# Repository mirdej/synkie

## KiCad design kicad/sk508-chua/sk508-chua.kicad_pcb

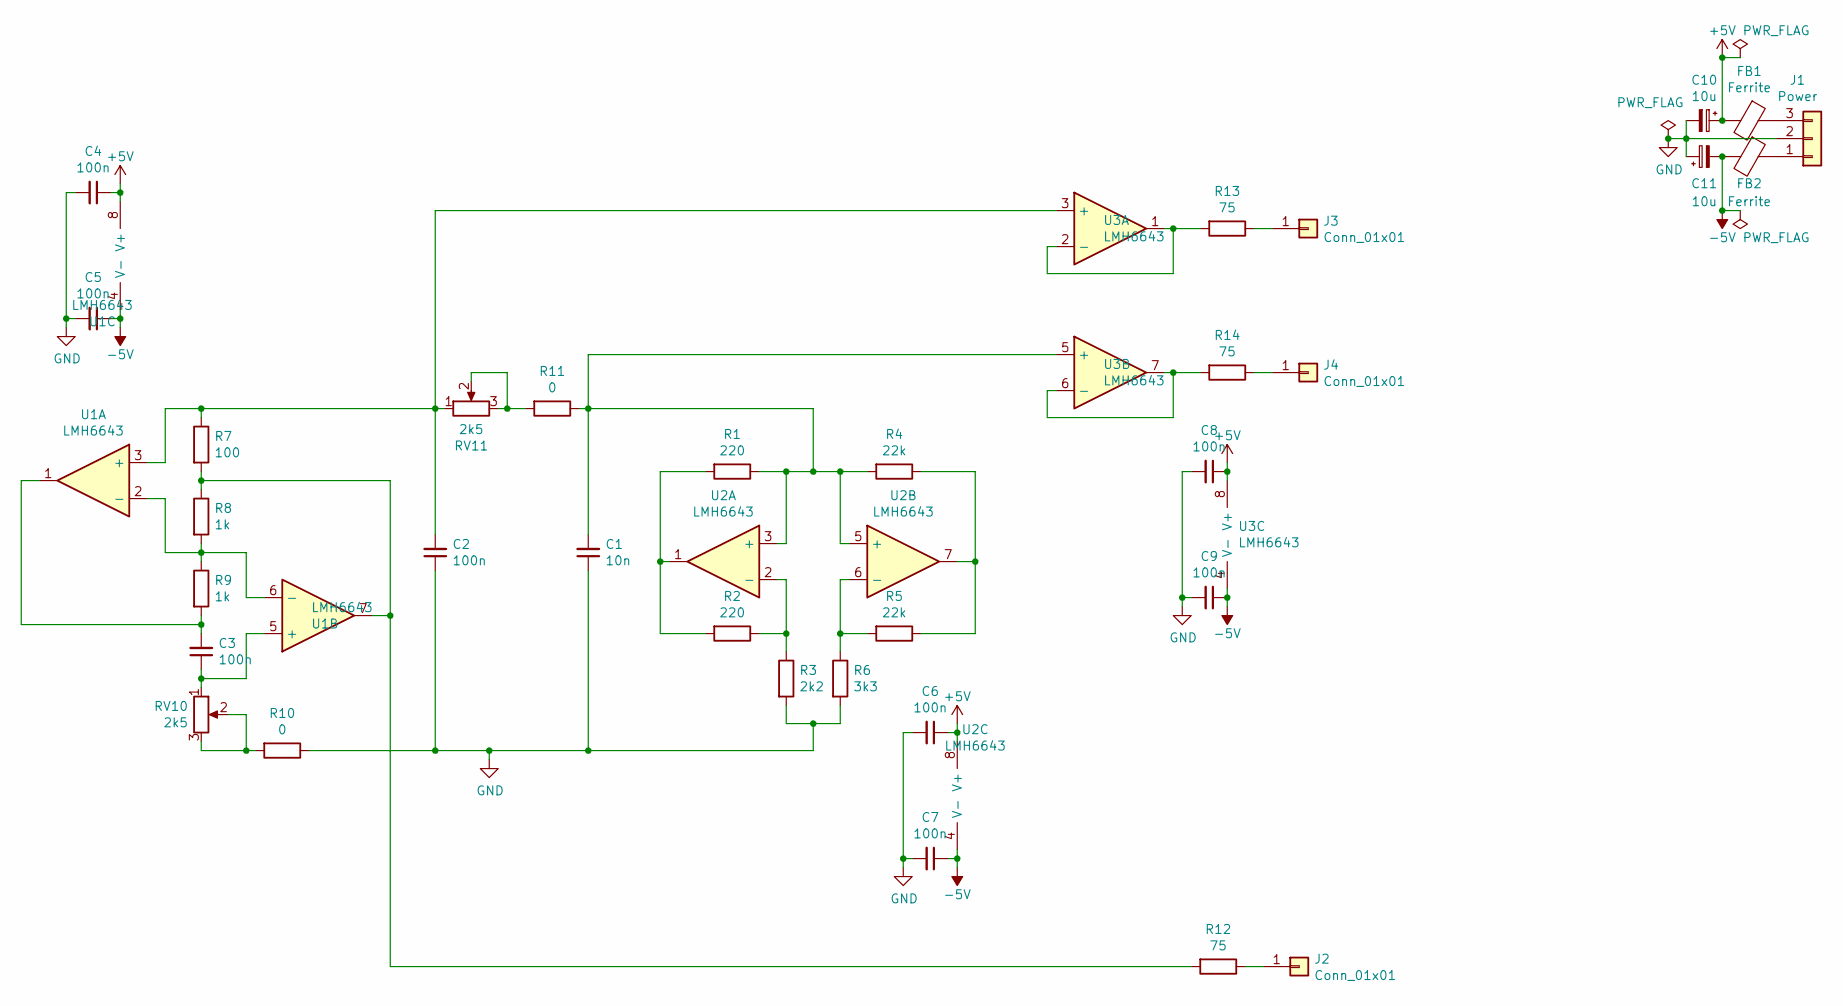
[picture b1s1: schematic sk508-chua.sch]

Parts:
C1: 10n; C_0805_2012Metric_Pad1.15x1.40mm_HandSolder
C2, C3, C4, C5, C6, C7, C8, C9: 100n; C_0603_1608Metric_Pad1.05x0.95mm_HandSolder
C10, C11: 10u; CP_EIA-3528-21_Kemet-B_Pad1.50x2.35mm_HandSolder
FB1, FB2: Ferrite; L_1206_3216Metric_Pad1.42x1.75mm_HandSolder
J1: Power; Molex_KK-254_AE-6410-03A_1x03_P2.54mm_Vertical
J2, J3, J4: Conn_01x01; Solderpad_1mm
R1, R2: 220; R_0805_2012Metric_Pad1.15x1.40mm_HandSolder
R3: 2k2; R_0805_2012Metric_Pad1.15x1.40mm_HandSolder
R4, R5: 22k; R_0805_2012Metric_Pad1.15x1.40mm_HandSolder
R6: 3k3; R_0805_2012Metric_Pad1.15x1.40mm_HandSolder
R7: 100; R_0805_2012Metric_Pad1.15x1.40mm_HandSolder
R8, R9: 1k; R_0805_2012Metric_Pad1.15x1.40mm_HandSolder
R10, R11: 0; R_0805_2012Metric_Pad1.15x1.40mm_HandSolder
R12, R13, R14: 75; R_0805_2012Metric_Pad1.15x1.40mm_HandSolder
RV10, RV11: 2k5; Potentiometer_Alps_RK09L_Single_Horizontal
U1, U2, U3: LMH6643; SOIC-8_3.9x4.9mm_P1.27mm

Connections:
+5V: C4.1, C6.1, C8.1, C10.1, FB1.2, U1.8 (V+), U2.8 (V+), U3.8 (V+)
-5V: C5.1, C7.1, C9.1, C11.2, FB2.2, U1.4 (V-), U2.4 (V-), U3.4 (V-)
GND: C1.1, C2.1, C4.2, C5.2, C6.2, C7.2, C8.2, C9.2, C10.2, C11.1, J1.2, R3.2, R6.2, R10.1
unnamed: C1.2, R1.1, R4.2, R11.1, U2.3 (+), U2.5 (+), U3.5 (+)
unnamed: C2.2, R7.1, RV11.1, U1.3 (+), U3.3 (+)
unnamed: C3.1, RV10.1, U1.5 (+)
unnamed: C3.2, R9.2, U1.1
unnamed: FB1.1, J1.3
unnamed: FB2.1, J1.1
unnamed: J2.1, R12.1
unnamed: J3.1, R13.1
unnamed: J4.1, R14.1
unnamed: R1.2, R2.2, U2.1
unnamed: R2.1, R3.1, U2.2 (-)
unnamed: R4.1, R5.1, U2.7
unnamed: R5.2, R6.1, U2.6 (-)
unnamed: R8.2, R9.1, U1.2 (-), U1.6 (-)
unnamed: R10.2, RV10.2, RV10.3
unnamed: R11.2, RV11.2, RV11.3
unnamed: R7.2, R8.1, R12.2, U1.7
unnamed: R13.2, U3.1, U3.2 (-)
unnamed: R14.2, U3.6 (-), U3.7

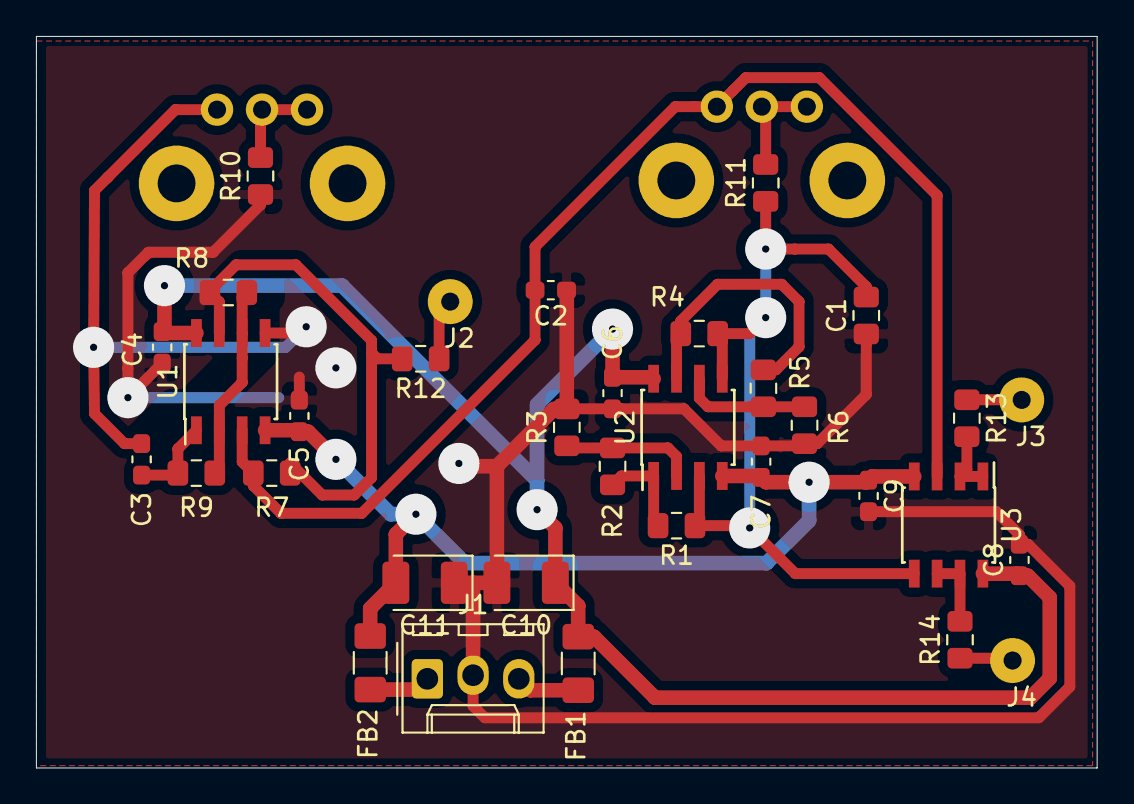
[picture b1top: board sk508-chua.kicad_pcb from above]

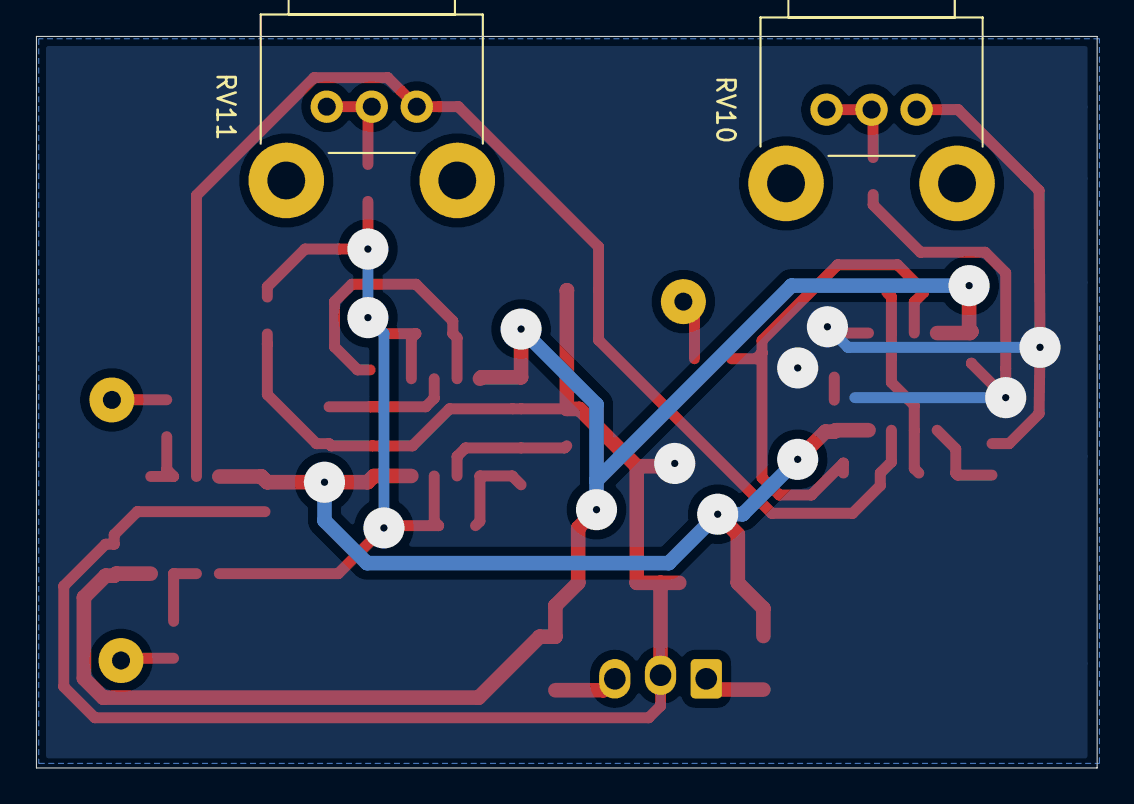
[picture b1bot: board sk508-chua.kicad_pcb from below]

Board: 2 copper layers, 58.9 x 40.6 mm, 36 parts (2 on the bottom side), 22 nets.

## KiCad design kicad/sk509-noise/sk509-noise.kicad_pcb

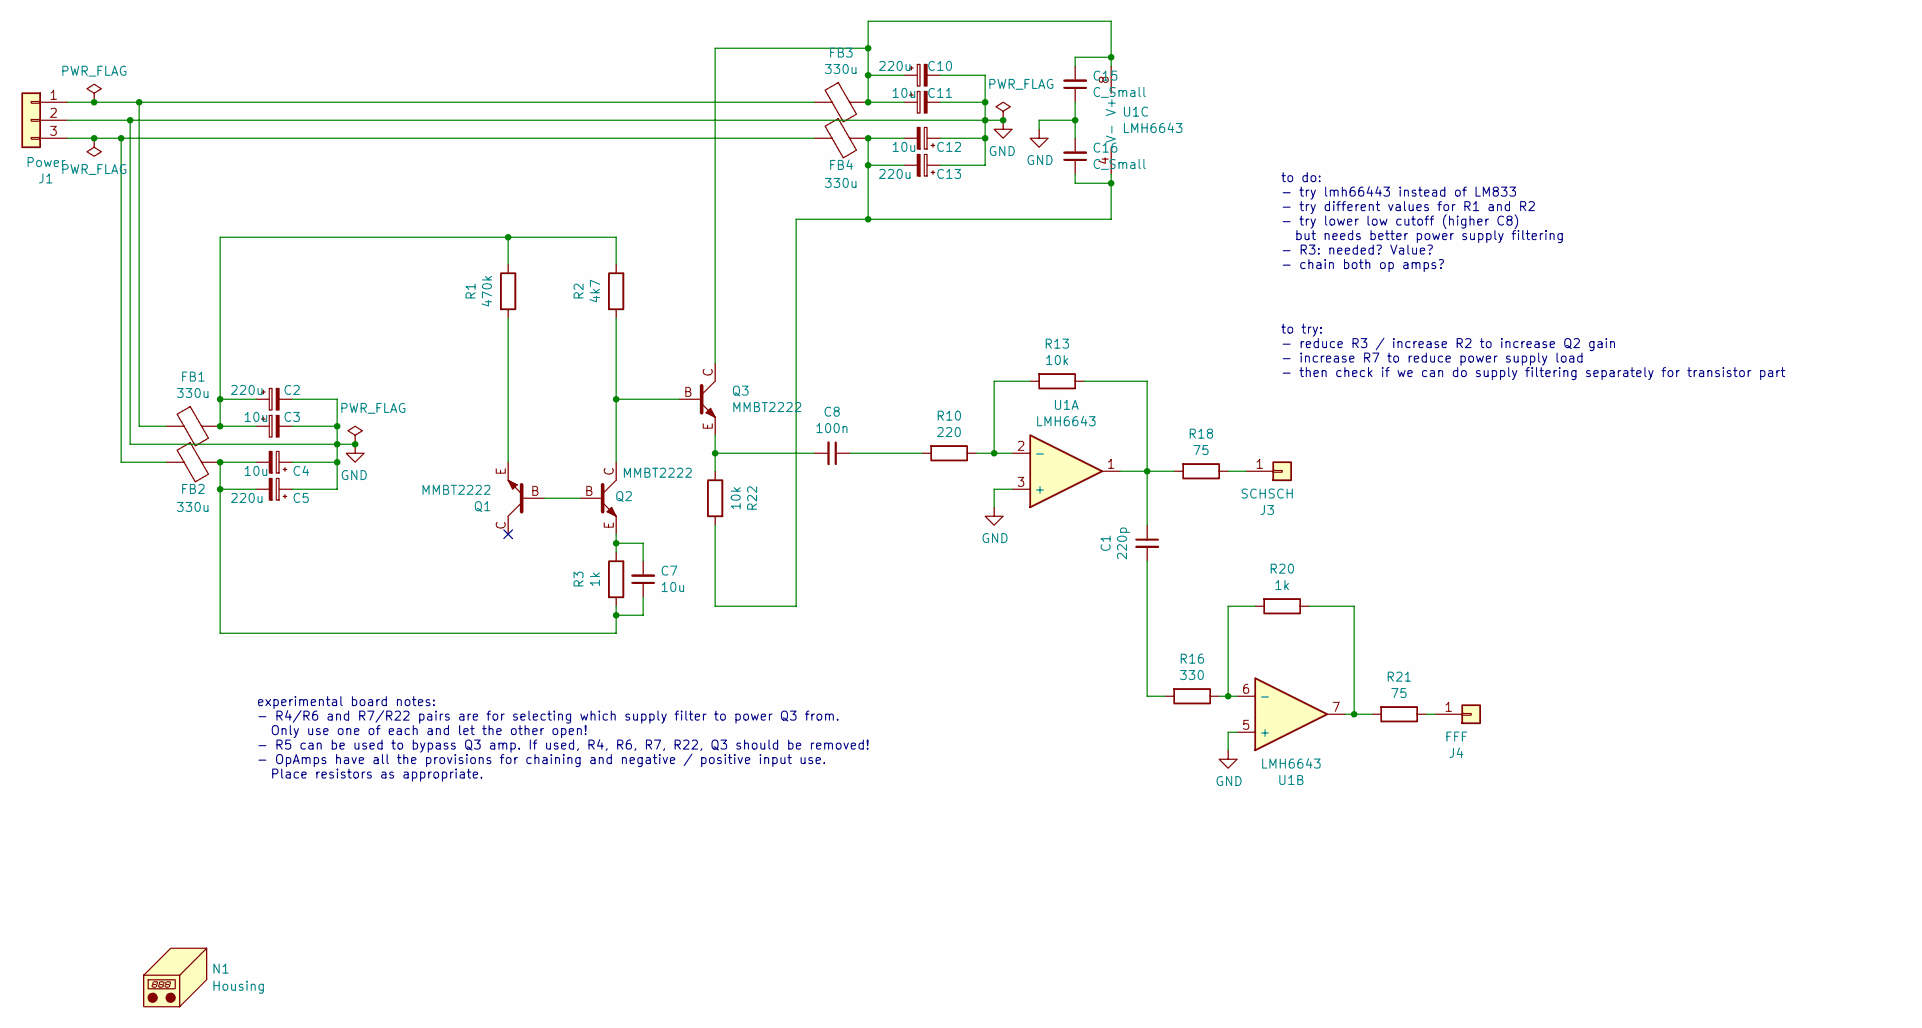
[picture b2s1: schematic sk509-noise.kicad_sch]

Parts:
C1: 220p; C_0805_2012Metric_Pad1.15x1.40mm_HandSolder
C2, C5, C10, C13: 220u; CP_EIA-3528-21_Kemet-B_Pad1.50x2.35mm_HandSolder
C3, C4, C11, C12: 10u; CP_EIA-3528-21_Kemet-B_Pad1.50x2.35mm_HandSolder
C7: 10u; C_0805_2012Metric_Pad1.15x1.40mm_HandSolder
C8: 100n; C_0805_2012Metric_Pad1.15x1.40mm_HandSolder
C15, C16: C_Small; C_0603_1608Metric_Pad1.05x0.95mm_HandSolder
FB1, FB2, FB3, FB4: 330u; L_1206_3216Metric_Pad1.42x1.75mm_HandSolder
J1: Power; Molex_KK-254_AE-6410-03A_1x03_P2.54mm_Vertical_SMD
J3: SCHSCH; Solderpad-SYNKIEPAD-2mm
J4: FFF; Solderpad-SYNKIEPAD-2mm
N1: Housing; Frontplate_20mm
Q1, Q2, Q3: MMBT2222; SOT-23_BEC
R1: 470k; R_0805_2012Metric_Pad1.15x1.40mm_HandSolder
R2: 4k7; R_0805_2012Metric_Pad1.15x1.40mm_HandSolder
R3, R20: 1k; R_0805_2012Metric_Pad1.15x1.40mm_HandSolder
R10: 220; R_0805_2012Metric_Pad1.15x1.40mm_HandSolder
R13, R22: 10k; R_0805_2012Metric_Pad1.15x1.40mm_HandSolder
R16: 330; R_0805_2012Metric_Pad1.15x1.40mm_HandSolder
R18, R21: 75; R_0805_2012Metric_Pad1.15x1.40mm_HandSolder
U1: LMH6643; SOIC-8_3.9x4.9mm_P1.27mm

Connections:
GND: C2.2, C3.2, C4.1, C5.1, C10.2, C11.2, C12.1, C13.1, C15.1, C16.2, J1.2, U1.3 (+), U1.5 (+)
unnamed: C1.1, R13.1, R18.2, U1.1
unnamed: C1.2, R16.2
unnamed: C2.1, C3.1, FB1.2, R1.1, R2.1
unnamed: C4.2, C5.2, C7.1, FB2.2, R3.2
unnamed: C7.2, Q2.E, R3.1
unnamed: C8.1, R10.2
unnamed: C8.2, Q3.E, R22.1
unnamed: FB1.1, FB3.1, J1.1
unnamed: FB2.1, FB4.1, J1.3
unnamed: J3.1, R18.1
unnamed: J4.1, R21.1
unnamed: Q1.B, Q2.B
unnamed: Q1.E, R1.2
unnamed: Q2.C, Q3.B, R2.2
unnamed: R20.1, R21.2, U1.7
unnamed: R10.1, R13.2, U1.2 (-)
unnamed: R16.1, R20.2, U1.6 (-)
unnamed: C10.1, C11.1, C15.2, FB3.2, Q3.C, U1.8 (V+)
unnamed: C12.2, C13.2, C16.1, FB4.2, R22.2, U1.4 (V-)

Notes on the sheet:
to do: - try lmh66443 instead of LM833 - try different values for R1 and R2 - try lower low cutoff (higher C8) but needs better power supply filtering - R3: needed? Value? - chain both op amps?
experimental board notes: - R4/R6 and R7/R22 pairs are for selecting which supply filter to power Q3 from. Only use one of each and let the other open! - R5 can be used to bypass Q3 amp. If used, R4, R6, R7, R22, Q3 should be removed! - OpAmps have all the provisions for chaining and negative / pos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
to try: - reduce R3 / increase R2 to increase Q2 gain - increase R7 to reduce power supply load - then check if we can do supply filtering separately for transistor part

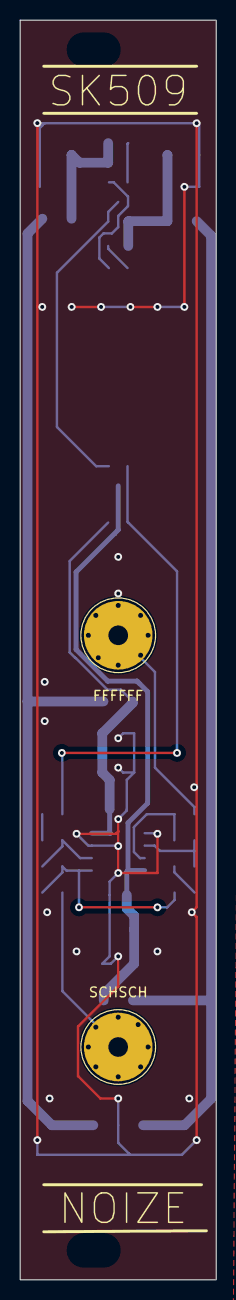
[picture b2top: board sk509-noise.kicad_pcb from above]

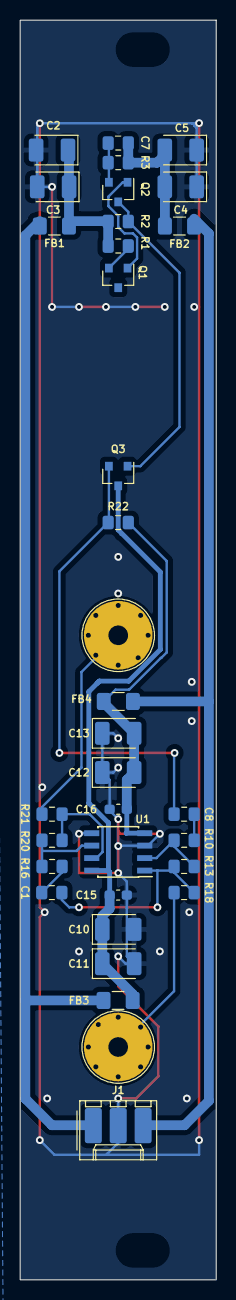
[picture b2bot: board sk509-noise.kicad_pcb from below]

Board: 2 copper layers, 20.0 x 128.5 mm, 35 parts (32 on the bottom side), 20 nets.

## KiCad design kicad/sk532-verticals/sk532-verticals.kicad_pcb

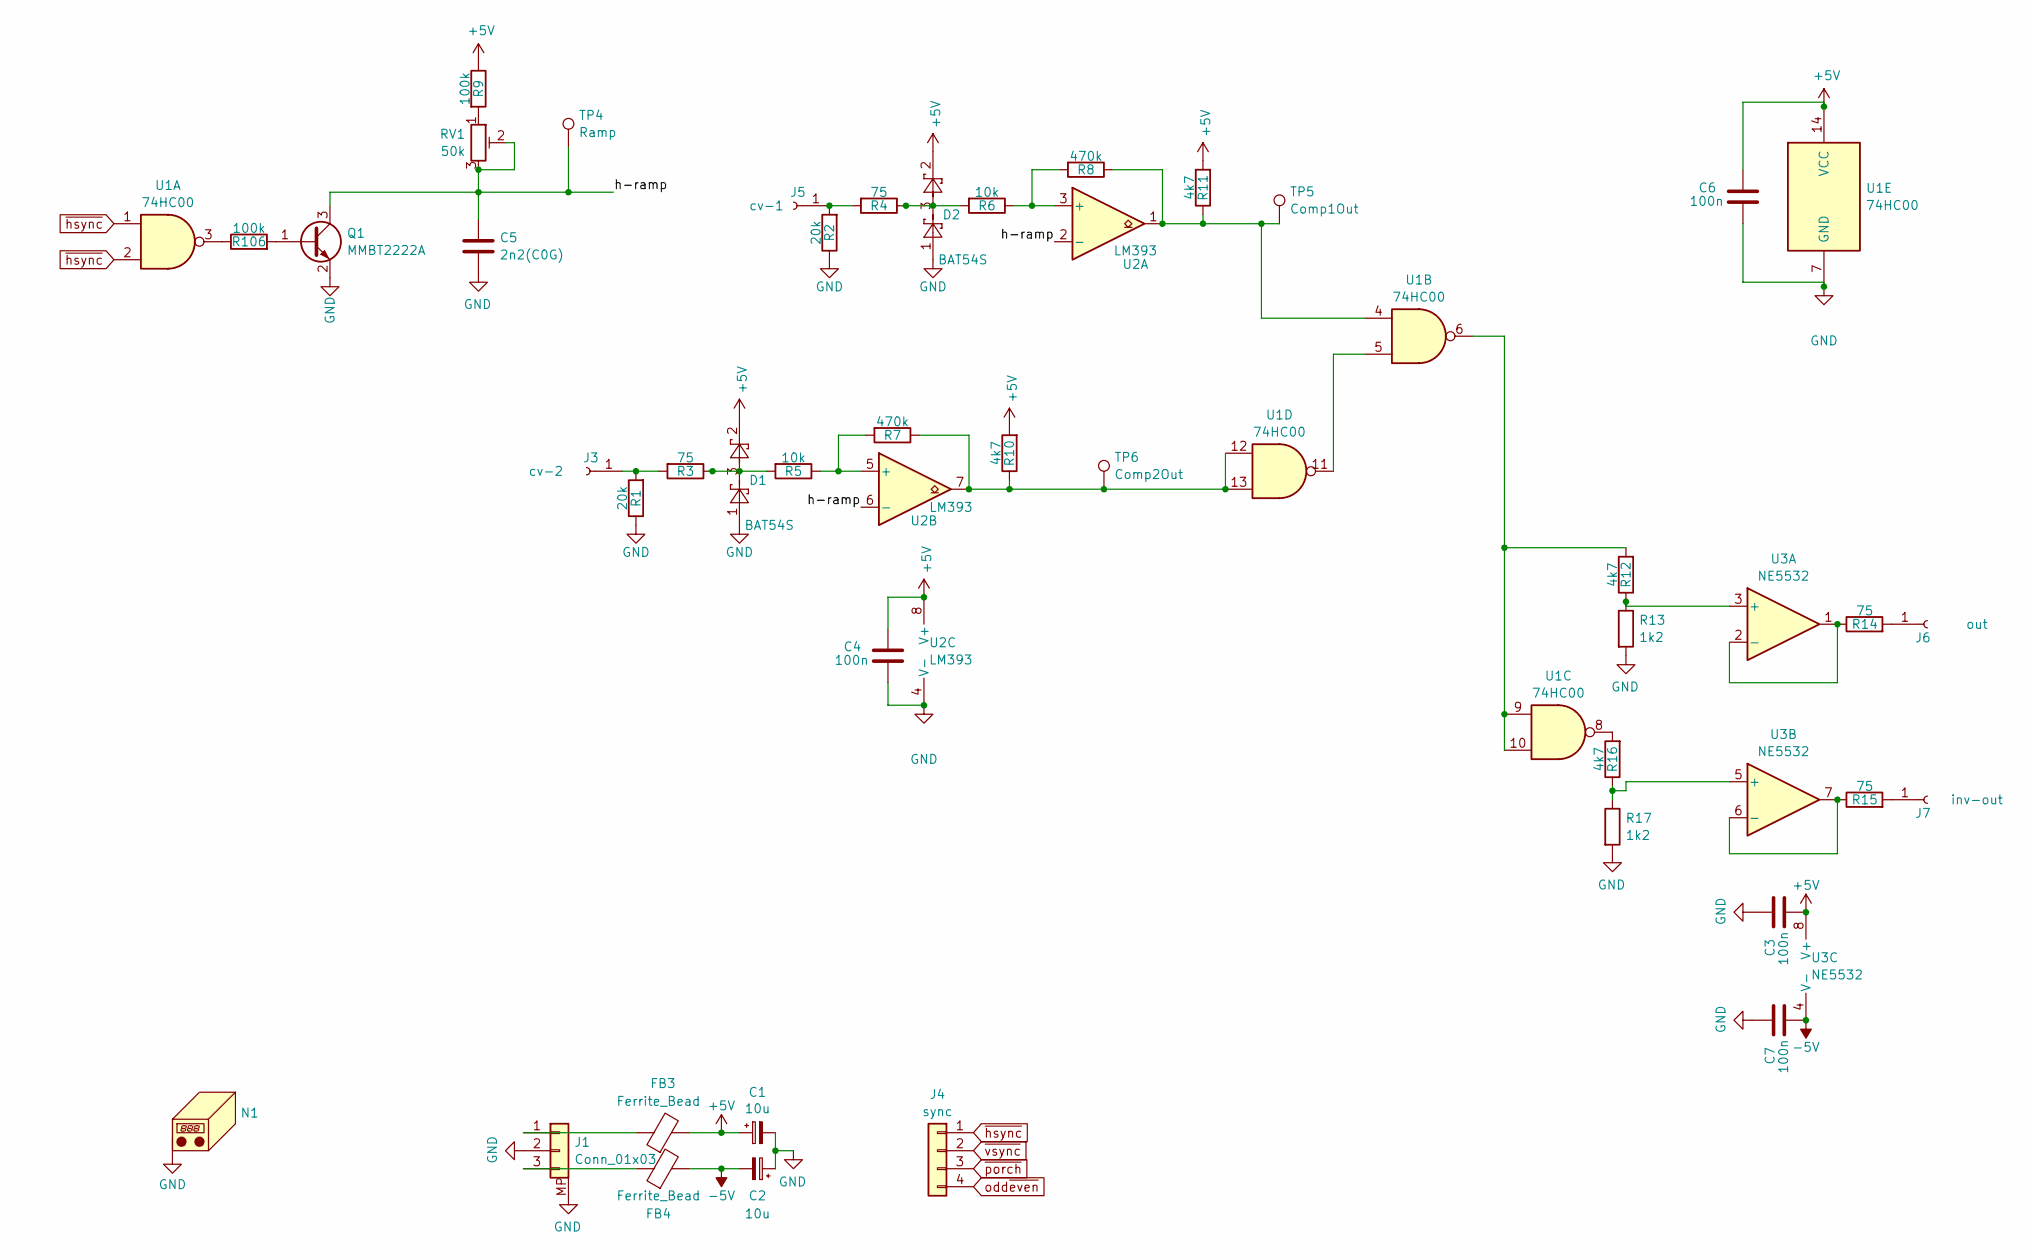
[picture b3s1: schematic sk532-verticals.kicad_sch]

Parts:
C1, C2: 10u; C_0805_2012Metric; LCSC C15850
C3, C4, C6, C7: 100n; C_0603_1608Metric; LCSC C14663
C5: 2n2(C0G); C_0805_2012Metric; LCSC C28260
D1, D2: BAT54S; SOT-23; LCSC C8592
FB3, FB4: Ferrite_Bead; L_0805_2012Metric; LCSC C1017
J1: Conn_01x03; Molex_PicoBlade_53398-0371_1x03-1MP_P1.25mm_Vertical; LCSC C293633
J3: cv-2; Banana2mm-Löthülse
J4: sync; Molex_PicoBlade_53398-0471_1x04-1MP_P1.25mm_Vertical; LCSC C17617036
J5: cv-1; Banana2mm-Löthülse
J6: out; Banana2mm-Löthülse
J7: inv-out; Banana2mm-Löthülse
N1: Housing_Pad; Frontplate_10mm
Q1: MMBT2222A; SOT-23; LCSC C8512
R1, R2: 20k; R_0603_1608Metric; LCSC C4184
R3, R4, R14, R15: 75; R_0603_1608Metric; LCSC C4275
R5, R6: 10k; R_0603_1608Metric; LCSC C25804
R7, R8: 470k; R_0603_1608Metric; LCSC C23178
R9, R106: 100k; R_0603_1608Metric; LCSC C25803
R10, R11, R12, R16: 4k7; R_0603_1608Metric; LCSC C23162
R13, R17: 1k2; LCSC C22765
RV1: 50k; Potentiometer_Bourns_3314J_Vertical; LCSC C50895
TP4: Ramp; TestPoint_Pad_D1.0mm
TP5: Comp1Out; TestPoint_Pad_D1.0mm
TP6: Comp2Out; TestPoint_Pad_D1.0mm
U1: 74HC00; SOIC-14_3.9x8.7mm_P1.27mm; LCSC C10090
U2: LM393; SOIC-8_3.9x4.9mm_P1.27mm; LCSC C7955
U3: NE5532; SOIC-8_3.9x4.9mm_P1.27mm; LCSC C7426

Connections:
+5V: C1.1, C3.2, C4.1, C6.1, D1.2, D2.2, FB3.2, R9.1, R10.2, R11.2, U1.14 (VCC), U2.8 (V+), U3.8 (V+)
-5V: C2.2, C7.2, FB4.2, U3.4 (V-)
/h-ramp: C5.1, Q1.3 (C), RV1.2, RV1.3, TP4.1 (1_1), U2.2 (-), U2.6 (-)
GND: C1.2, C2.1, C3.1, C4.2, C5.2, C6.2, C7.1, D1.1, D2.1, J1.2, J1.MP, N1.1 (PAD_1), Q1.2 (E), R1.1, R2.1, R13.2, R17.2, U1.7 (GND), U2.4 (V-)
unnamed: D1.3, R3.1, R5.2
unnamed: D2.3, R4.1, R6.2
unnamed: FB3.1, J1.1
unnamed: FB4.1, J1.3
unnamed: J3.1 (Pin_1_1), R1.2, R3.2
unnamed: J5.1 (Pin_1_1), R2.2, R4.2
unnamed: J6.1 (Pin_1_1), R14.2
unnamed: J7.1 (Pin_1_1), R15.2
unnamed: Q1.1 (B), R106.2
unnamed: R9.2, RV1.1
unnamed: R7.1, R10.1, TP6.1 (1_1), U1.12, U1.13, U2.7
unnamed: R8.1, R11.1, TP5.1 (1_1), U1.4, U2.1
unnamed: R12.2, U1.6, U1.9, U1.10
unnamed: R16.2, U1.8
unnamed: R106.1, U1.3
unnamed: U1.5, U1.11
unnamed: R6.1, R8.2, U2.3 (+)
unnamed: R5.1, R7.2, U2.5 (+)
unnamed: R12.1, R13.1, U3.3 (+)
unnamed: R14.1, U3.1, U3.2 (-)
unnamed: R16.1, R17.1, U3.5 (+)
unnamed: R15.1, U3.6 (-), U3.7
odd~even: J4.4
~hsync: J4.1, U1.1, U1.2
~porch: J4.3
~vsync: J4.2

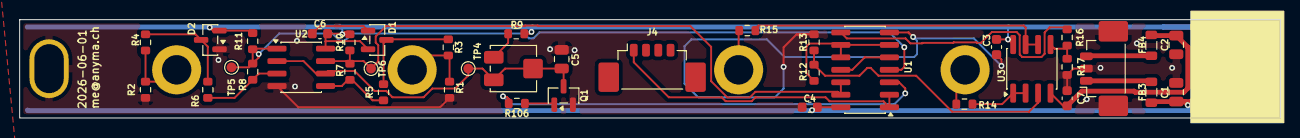
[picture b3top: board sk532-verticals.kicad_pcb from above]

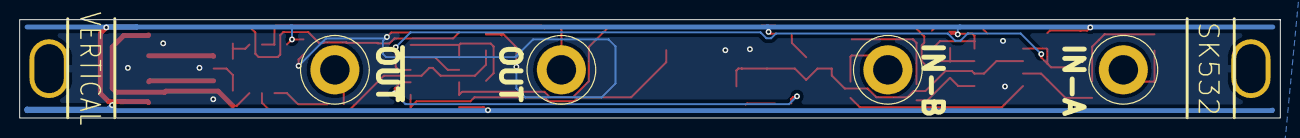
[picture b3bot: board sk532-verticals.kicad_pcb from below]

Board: 2 copper layers, 128.5 x 10.0 mm, 44 parts (5 on the bottom side), 27 nets.

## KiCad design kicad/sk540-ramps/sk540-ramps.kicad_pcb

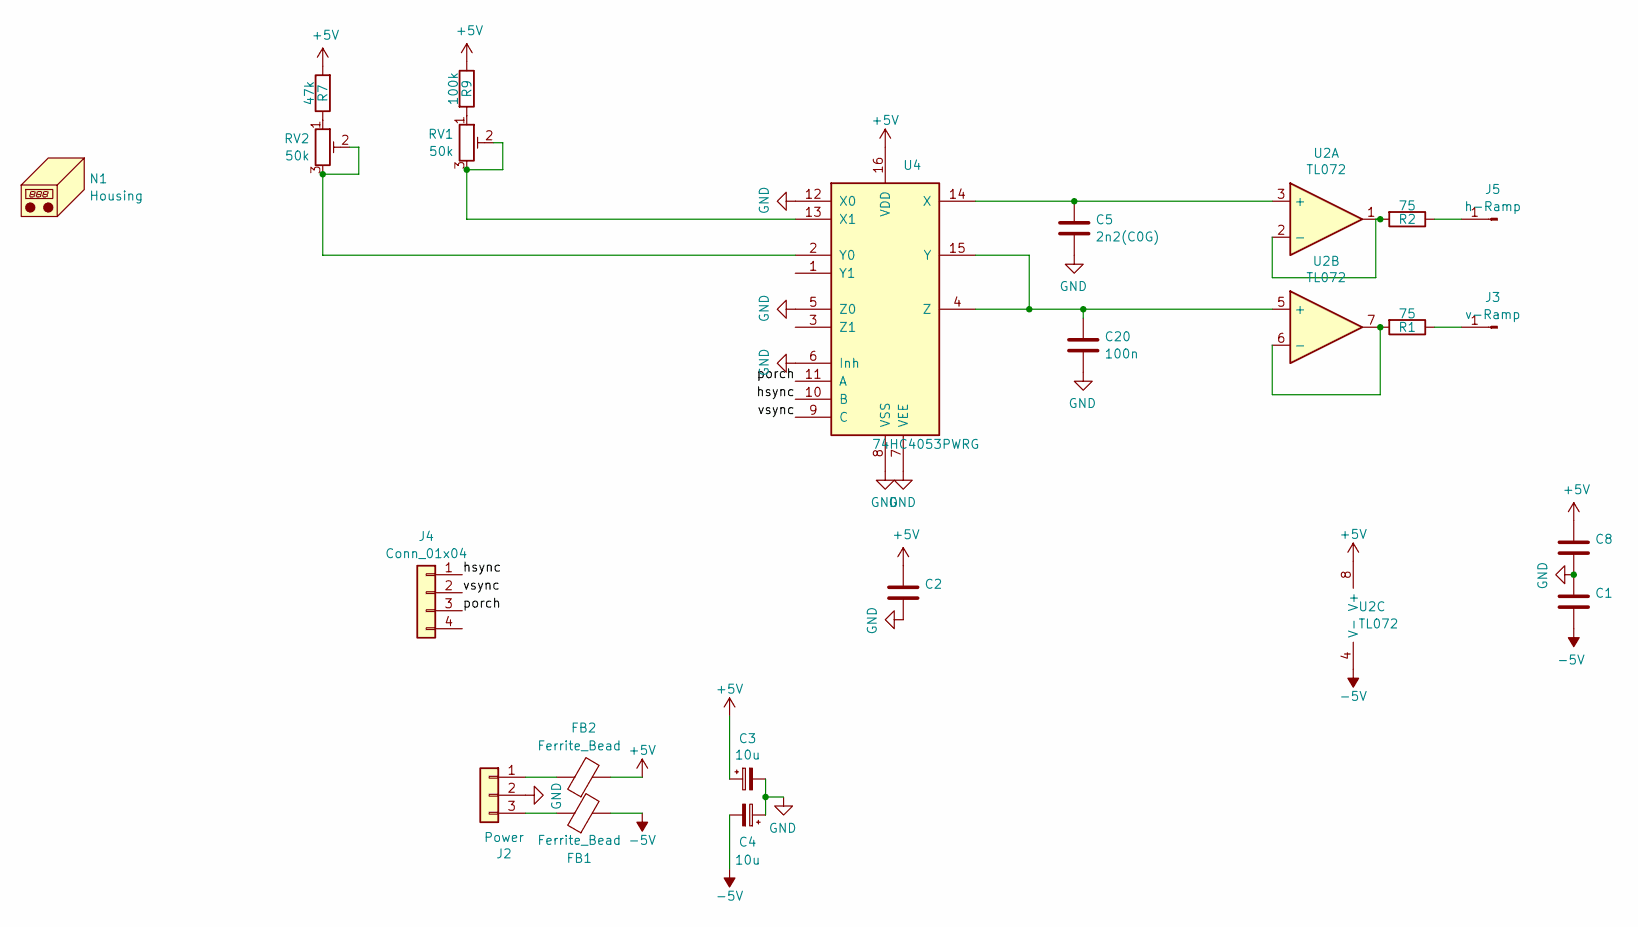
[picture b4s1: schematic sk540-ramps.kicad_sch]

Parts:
C1, C2, C8, C20: 100n; C_0603_1608Metric; LCSC C14663
C3, C4: 10u; C_0805_2012Metric; LCSC C15850
C5: 2n2(C0G); C_0805_2012Metric; LCSC C28260
FB1, FB2: Ferrite_Bead; L_0805_2012Metric; LCSC C1017
J2: Power; Molex_KK-254_AE-6410-03A_1x03_P2.54mm_Vertical_SMD
J3: v-Ramp; Banana2mm-Löthülse
J4: Conn_01x04; Molex_KK-254_AE-6410-04A_1x04_P2.54mm_Vertical_SMD
J5: h-Ramp; Banana2mm-Löthülse
N1: Housing; Frontplate_10mm
R1, R2: 75; R_0603_1608Metric; LCSC C4275
R7: 47k; R_0603_1608Metric; LCSC C25819
R9: 100k; R_0603_1608Metric; LCSC C25803
RV1, RV2: 50k; Potentiometer_Bourns_3314J_Vertical; LCSC C50895
U2: TL072; SO-8_3.9x4.9mm_P1.27mm; LCSC C6961
U4: 74HC4053PWRG; TSSOP-16_4.4x5mm_P0.65mm; LCSC C19723809

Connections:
+5V: C2.1, C3.1, C8.1, FB2.2, R7.2, R9.1, U2.8 (V+), U4.16 (VDD)
-5V: C1.2, C4.2, FB1.2, U2.4 (V-)
/hsync: J4.1, U4.10 (B)
/porch: J4.3, U4.11 (A)
/vsync: J4.2, U4.9 (C)
GND: C1.1, C2.2, C3.2, C4.1, C5.2, C8.2, C20.1, J2.2, U4.5 (Z0), U4.6 (Inh), U4.7 (VEE), U4.8 (VSS), U4.12 (X0)
unnamed: FB2.1, J2.1
unnamed: FB1.1, J2.3
unnamed: J3.1, R1.1
unnamed: J5.1, R2.1
unnamed: R7.1, RV2.1
unnamed: R9.2, RV1.1
unnamed: C5.1, U2.3 (+), U4.14 (X)
unnamed: R2.2, U2.1, U2.2 (-)
unnamed: C20.2, U2.5 (+), U4.4 (Z), U4.15 (Y)
unnamed: R1.2, U2.6 (-), U2.7
unnamed: RV1.2, RV1.3, U4.13 (X1)
unnamed: RV2.2, RV2.3, U4.2 (Y0)

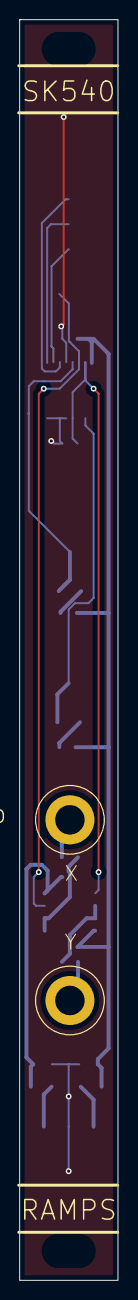
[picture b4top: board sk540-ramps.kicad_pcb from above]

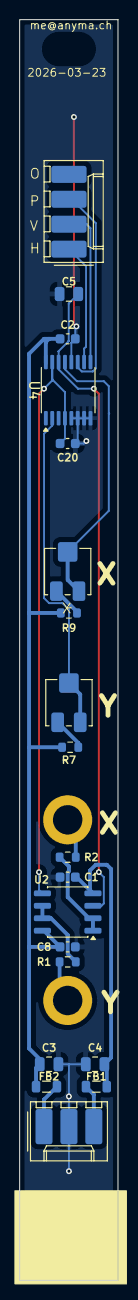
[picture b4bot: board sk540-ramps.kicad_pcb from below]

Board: 2 copper layers, 10.0 x 128.5 mm, 22 parts (19 on the bottom side), 18 nets.

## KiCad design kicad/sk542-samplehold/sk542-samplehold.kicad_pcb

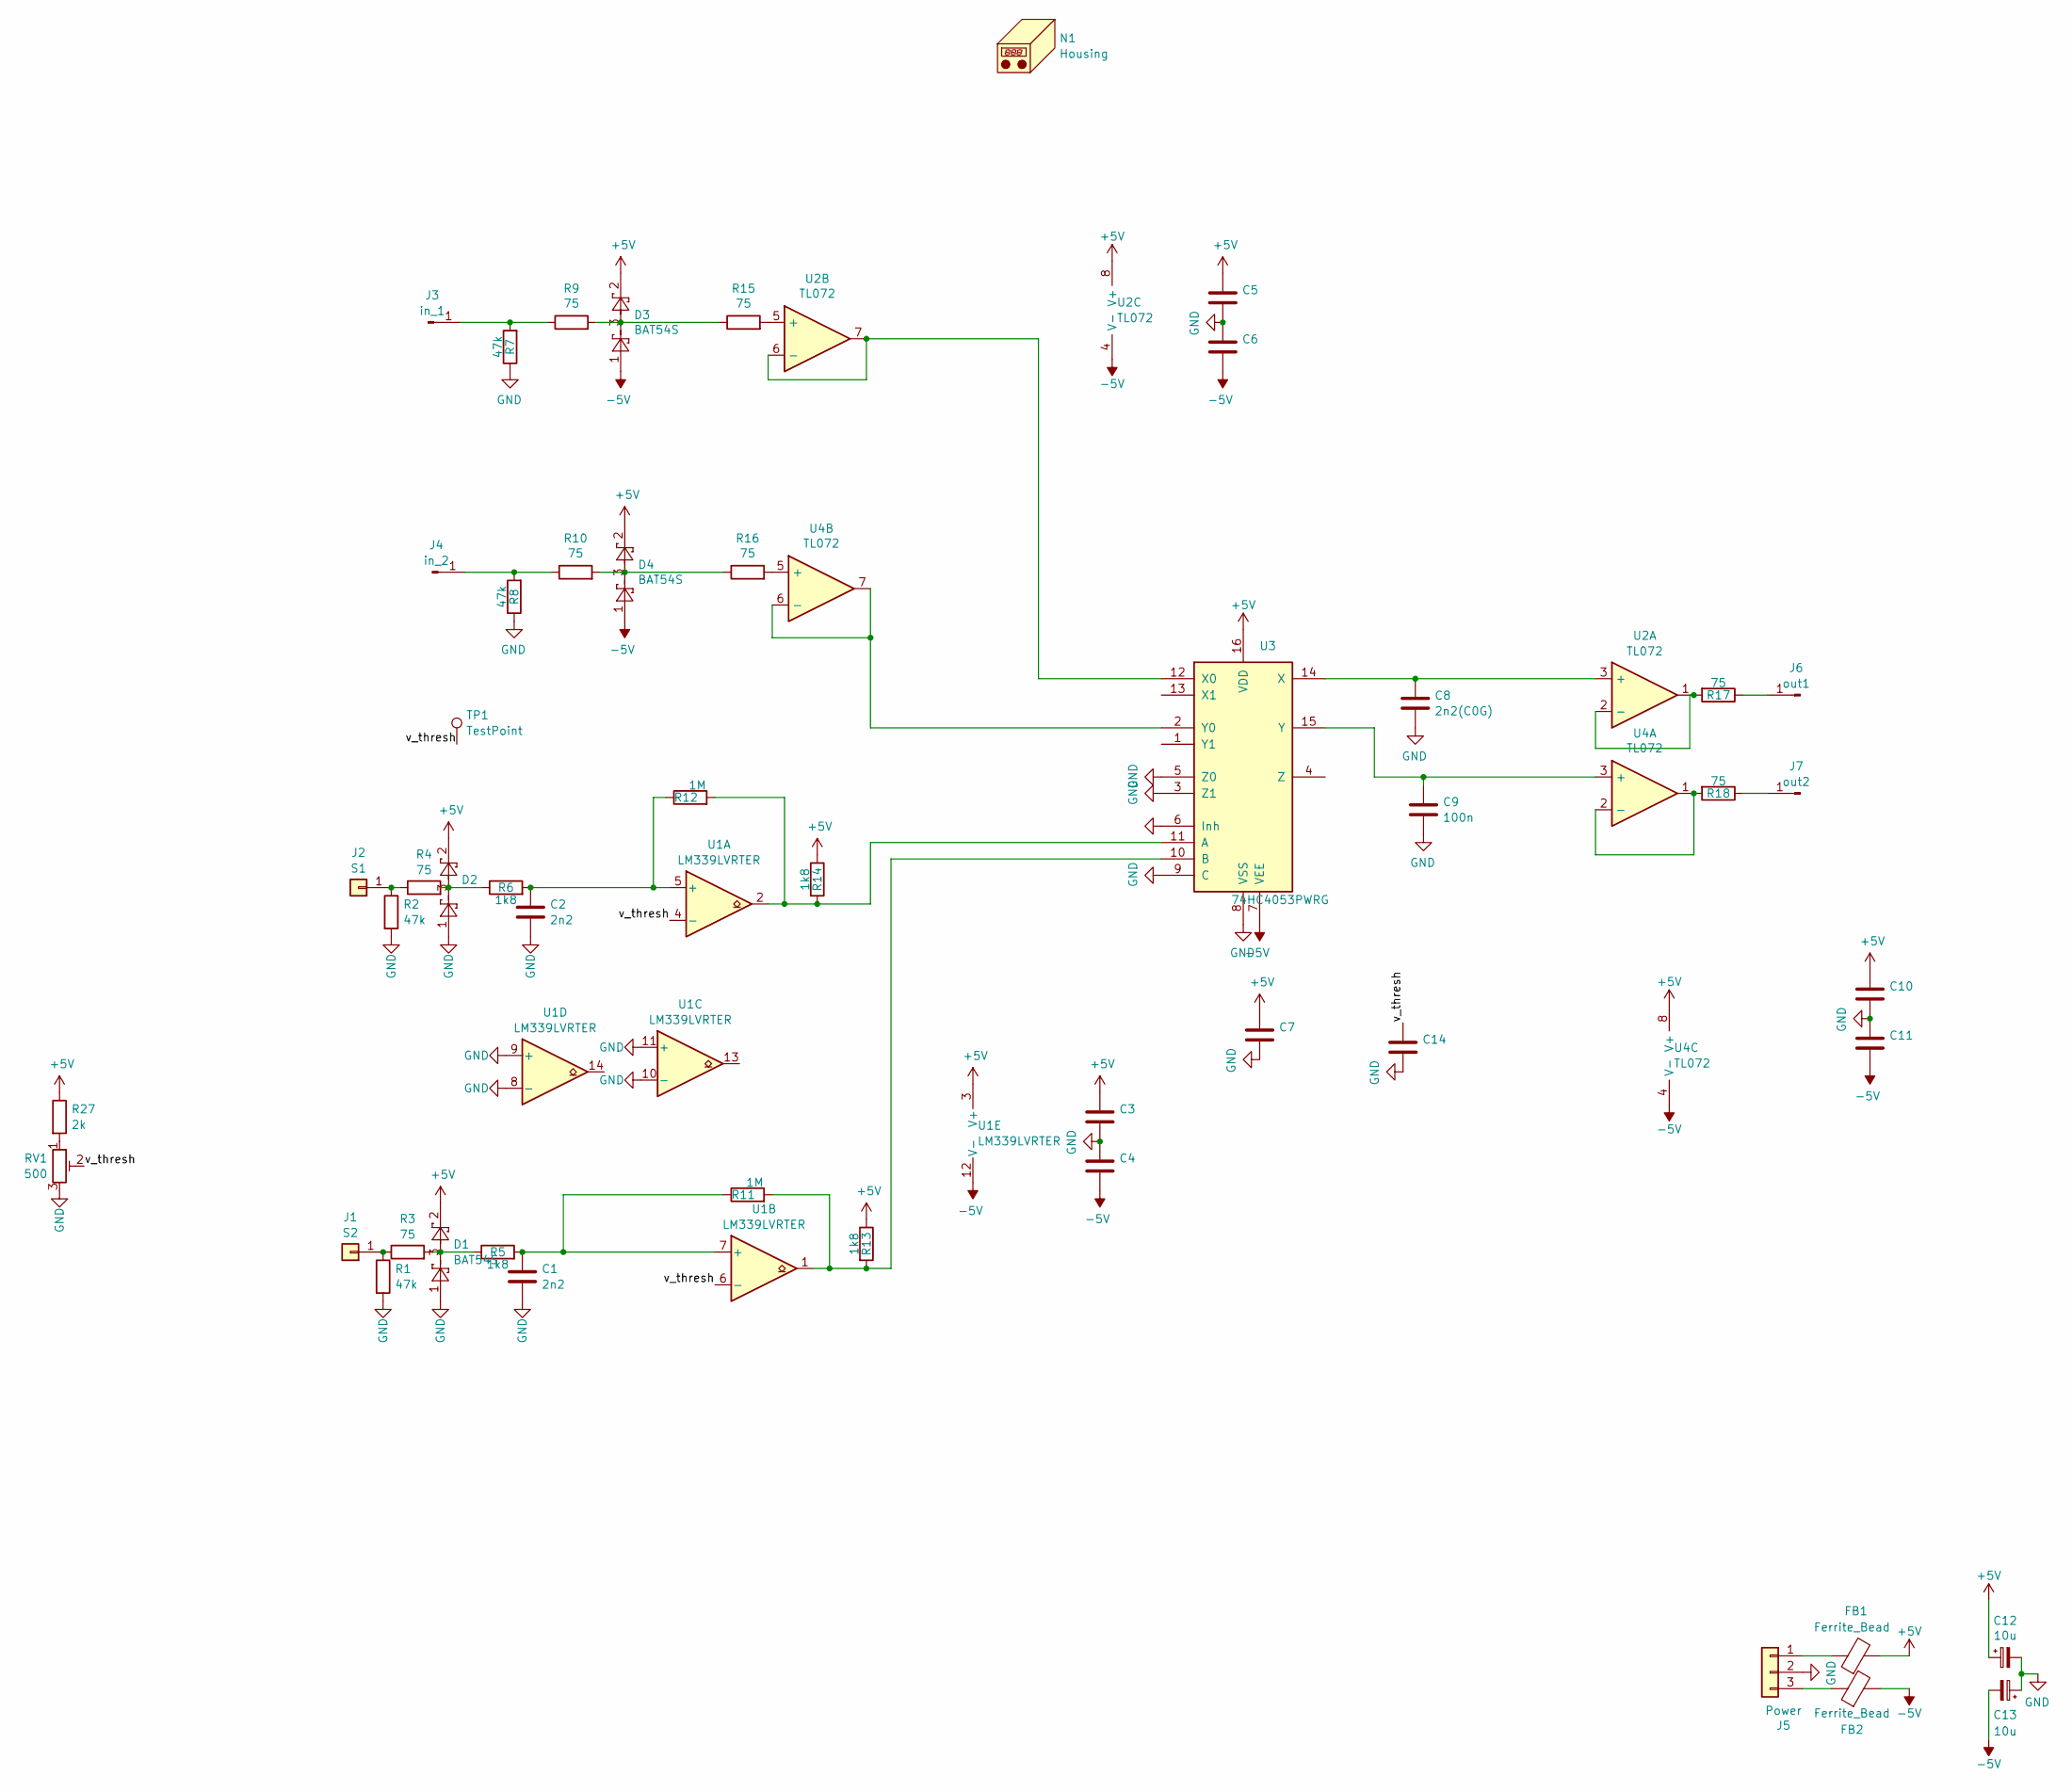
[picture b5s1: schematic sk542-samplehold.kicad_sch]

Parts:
C1, C2: 2n2; C_0603_1608Metric; LCSC C1604
C3, C4, C5, C6, C7, C9, C10, C11, C14: 100n; C_0603_1608Metric; LCSC C14663
C8: 2n2(C0G); C_0805_2012Metric; LCSC C28260
C12, C13: 10u; C_0805_2012Metric; LCSC C15850
D1, D2, D3, D4: BAT54S; SOT-23; LCSC C8592
FB1, FB2: Ferrite_Bead; L_0805_2012Metric; LCSC C1017
J1: S2; Banana2mm-Löthülse
J2: S1; Banana2mm-Löthülse
J3: in_1; Banana2mm-Löthülse
J4: in_2; Banana2mm-Löthülse
J5: Power; Molex_KK-254_AE-6410-03A_1x03_P2.54mm_Vertical_SMD
J6: out1; Banana2mm-Löthülse
J7: out2; Banana2mm-Löthülse
N1: Housing; Frontplate_10mm
R1, R2, R7, R8: 47k; R_0603_1608Metric; LCSC C25819
R3, R4, R9, R10, R15, R16, R17, R18: 75; R_0603_1608Metric; LCSC C4275
R5, R6, R13, R14: 1k8; R_0603_1608Metric; LCSC C4177
R11, R12: 1M; R_0603_1608Metric; LCSC C22935
R27: 2k; R_0805_2012Metric_Pad1.15x1.40mm_HandSolder; LCSC C17604
RV1: 500; Potentiometer_Bourns_3314J_Vertical; LCSC C123873
TP1: TestPoint; TestPoint_Pad_2.5x2.5mm
U1: LM339LVRTER; WQFN-16-1EP_3x3mm_P0.5mm_EP1.6x1.6mm; LCSC C3658606
U2, U4: TL072; SO-8_3.9x4.9mm_P1.27mm; LCSC C6961
U3: 74HC4053PWRG; TSSOP-16_4.4x5mm_P0.65mm; LCSC C19723809

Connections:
+5V: C3.1, C5.1, C7.1, C10.1, C12.1, D1.2, D2.2, D3.2, D4.2, FB1.2, R13.1, R14.1, R27.1, U1.3 (V+), U2.8 (V+), U3.16 (VDD), U4.8 (V+)
-5V: C4.2, C6.2, C11.2, C13.2, D3.1, D4.1, FB2.2, U1.12 (V-), U2.4 (V-), U3.7 (VEE), U4.4 (V-)
/v_thresh: C14.1, RV1.2, TP1.1, U1.4 (-), U1.6 (-)
GND: C1.2, C2.2, C3.2, C4.1, C5.2, C6.1, C7.2, C8.2, C9.1, C10.2, C11.1, C12.2, C13.1, C14.2, D1.1, D2.1, J5.2, R1.2, R2.2, R7.1, R8.1, RV1.3, U1.8 (-), U1.9 (+), U1.10 (-), U1.11 (+), U3.3 (Z1), U3.5 (Z0), U3.6 (Inh), U3.8 (VSS), U3.9 (C)
unnamed: D1.3, R3.2, R5.1
unnamed: D2.3, R4.2, R6.1
unnamed: D3.3, R9.2, R15.1
unnamed: D4.3, R10.2, R16.1
unnamed: J1.1, R1.1, R3.1
unnamed: J2.1, R2.1, R4.1
unnamed: J3.1, R7.2, R9.1
unnamed: J4.1, R8.2, R10.1
unnamed: FB1.1, J5.1
unnamed: FB2.1, J5.3
unnamed: J6.1, R17.1
unnamed: J7.1, R18.1
unnamed: R27.2, RV1.1
unnamed: C2.1, R6.2, R12.1, U1.5 (+)
unnamed: C1.1, R5.2, R11.1, U1.7 (+)
unnamed: C8.1, U2.3 (+), U3.14 (X)
unnamed: R17.2, U2.1, U2.2 (-)
unnamed: R15.2, U2.5 (+)
unnamed: U2.6 (-), U2.7, U3.12 (X0)
unnamed: R12.2, R14.2, U1.2, U3.11 (A)
unnamed: R11.2, R13.2, U1.1, U3.10 (B)
unnamed: U3.2 (Y0), U4.6 (-), U4.7
unnamed: C9.2, U3.15 (Y), U4.3 (+)
unnamed: R18.2, U4.1, U4.2 (-)
unnamed: R16.2, U4.5 (+)

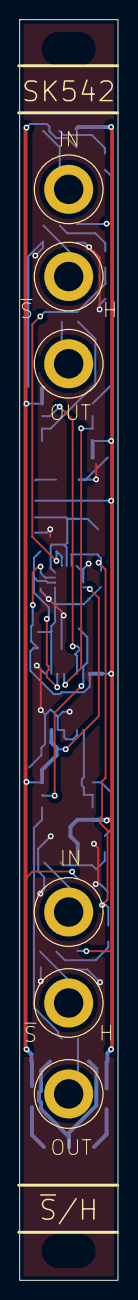
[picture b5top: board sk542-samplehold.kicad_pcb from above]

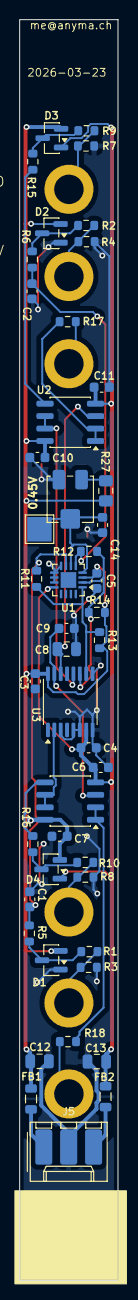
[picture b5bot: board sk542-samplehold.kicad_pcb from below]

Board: 2 copper layers, 10.0 x 128.5 mm, 53 parts (46 on the bottom side), 29 nets.
